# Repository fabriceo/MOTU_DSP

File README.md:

# MOTU_DSP
A DSP module compatible with MOTU 8A or MOTU 624

This repository contains Schematics, component placement for the MOTU_DSP board.
and additional documentation as PDF files.

this design is subject to Creative Commons Attribution Share-Alike 4.0 license

thread on diyaudio.com can be found here : https://www.diyaudio.com/forums/digital-line-level/333855-dsp-module-compatible-motu-8a-624-a.html

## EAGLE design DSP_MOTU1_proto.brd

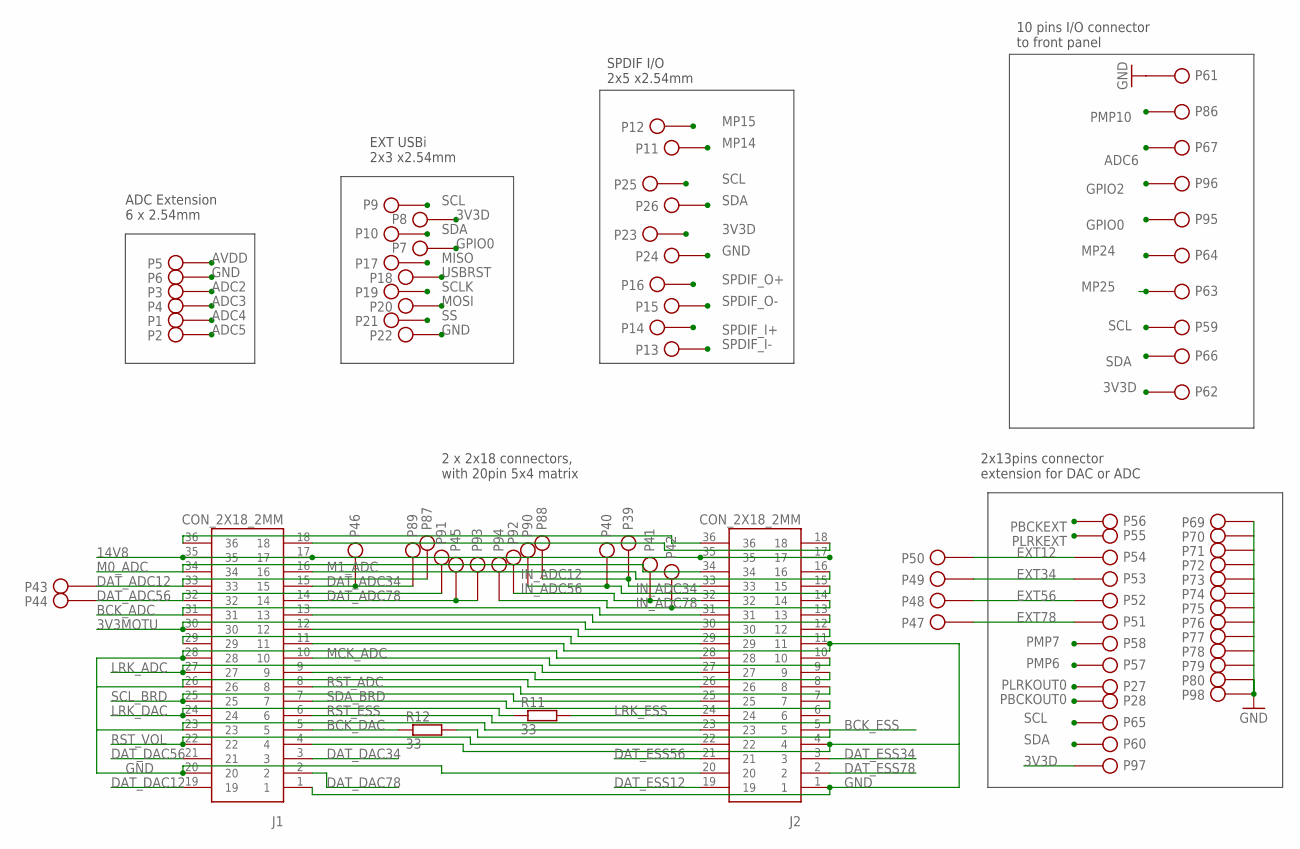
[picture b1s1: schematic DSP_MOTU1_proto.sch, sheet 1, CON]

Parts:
J1, J2: CON_2X18_2MM
P1, P2, P3, P4, P5, P6, P7, P8, P9, P10, P11, P12, P13, P14, P15, P16, P17, P18, P19, P20, P21, P22, P23, P24, P25, P26, P27, P28, P39, P40, P41, P42, P43, P44, P45, P46, P47, P48, P49, P50, P51, P52, P53, P54, P55, P56, P57, P58, P59, P60, P61, P62, P63, P64, P65, P66, P67, P69, P70, P71, P72, P73, P74, P75, P76, P77, P78, P79, P80, P86, P87, P88, P89, P90, P91, P92, P93, P94, P95, P96, P97, P98: PIN_254
R11, R12: 33; R0805

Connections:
3V3D: P8.1, P23.1, P62.1, P97.1; also elsewhere on the board
3V3MOTU: J1.30, J2.30
14V8: J1.17, J1.35, J2.17, J2.35; also elsewhere on the board
ADC2: P3.1; also elsewhere on the board
ADC3: P4.1; also elsewhere on the board
ADC4: P1.1; also elsewhere on the board
ADC5: P2.1; also elsewhere on the board
ADC6: P67.1; also elsewhere on the board
AVDD: P5.1; also elsewhere on the board
BCK_ADC: J1.31, J2.31; also elsewhere on the board
BCK_DAC: J1.5, R12.1; also elsewhere on the board
BCK_ESS: J2.5, R12.2; also elsewhere on the board
DAT_ADC12: J1.33, P43.1, P87.1
DAT_ADC34: J1.15, P46.1, P89.1
DAT_ADC56: J1.32, P44.1, P91.1
DAT_ADC78: J1.14, P45.1, P93.1
DAT_DAC12: J1.19; also elsewhere on the board
DAT_DAC34: J1.3; also elsewhere on the board
DAT_DAC56: J1.21; also elsewhere on the board
DAT_DAC78: J1.2; also elsewhere on the board
DAT_ESS12: J2.19; also elsewhere on the board
DAT_ESS34: J2.3; also elsewhere on the board
DAT_ESS56: J2.21; also elsewhere on the board
DAT_ESS78: J2.2; also elsewhere on the board
EXT12: P50.1, P54.1
EXT34: P49.1, P53.1
EXT56: P48.1, P52.1
EXT78: P47.1, P51.1
GND: J1.1, J1.4, J1.11, J1.20, J1.23, J1.26, J1.28, J2.1, J2.4, J2.11, J2.20, J2.23, J2.26, J2.28, P6.1, P22.1, P24.1, P61.1, P69.1, P70.1, P71.1, P72.1, P73.1, P74.1, P75.1, P76.1, P77.1, P78.1, P79.1, P80.1, P98.1; also elsewhere on the board
GPIO0: P7.1, P95.1; also elsewhere on the board
GPIO2: P96.1; also elsewhere on the board
IN_ADC12: J2.33, P39.1, P88.1
IN_ADC34: J2.15, P40.1, P90.1
IN_ADC56: J2.32, P41.1, P92.1
IN_ADC78: J2.14, P42.1, P94.1
LRK_ADC: J1.27, J2.27; also elsewhere on the board
LRK_DAC: J1.24, R11.1; also elsewhere on the board
LRK_ESS: J2.24, R11.2; also elsewhere on the board
M0_ADC: J1.34, J2.34
M1_ADC: J1.16, J2.16
MCK_ADC: J1.10, J2.10
MISO: P17.1; also elsewhere on the board
MOSI: P20.1; also elsewhere on the board
MP14: P11.1; also elsewhere on the board
MP15: P12.1; also elsewhere on the board
MP24: P64.1; also elsewhere on the board
MP25: P63.1; also elsewhere on the board
unnamed: J1.9, J2.9
unnamed: J1.29, J2.29
unnamed: J1.12, J2.12
unnamed: J1.13, J2.13
unnamed: J1.18, J2.18
unnamed: J1.36, J2.36
PBCKEXT: P56.1; also elsewhere on the board
PBCKOUT0: P28.1; also elsewhere on the board
PLRKEXT: P55.1; also elsewhere on the board
PLRKOUT0: P27.1; also elsewhere on the board
PMP6: P57.1; also elsewhere on the board
PMP7: P58.1; also elsewhere on the board
PMP10: P86.1; also elsewhere on the board
RST_ADC: J1.8, J2.8
RST_ESS: J1.6, J2.6
RST_VOL: J1.22, J2.22; also elsewhere on the board
SCL: P9.1, P25.1, P59.1, P65.1; also elsewhere on the board
SCLK: P19.1; also elsewhere on the board
SCL_BRD: J1.25, J2.25
SDA: P10.1, P26.1, P60.1, P66.1; also elsewhere on the board
SDA_BRD: J1.7, J2.7
SPDIF_I+: P14.1; also elsewhere on the board
SPDIF_I-: P13.1; also elsewhere on the board
SPDIF_O+: P16.1; also elsewhere on the board
SPDIF_O-: P15.1; also elsewhere on the board
SS: P21.1; also elsewhere on the board
USBRST: P18.1; also elsewhere on the board

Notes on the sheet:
ADC Extension 6 x 2.54mm
EXT USBi 2x3 x2.54mm
SPDIF I/O 2x5 x2.54mm
2x13pins connector extension for DAC or ADC
10 pins I/O connector to front panel
2 x 2x18 connectors, with 20pin 5x4 matrix

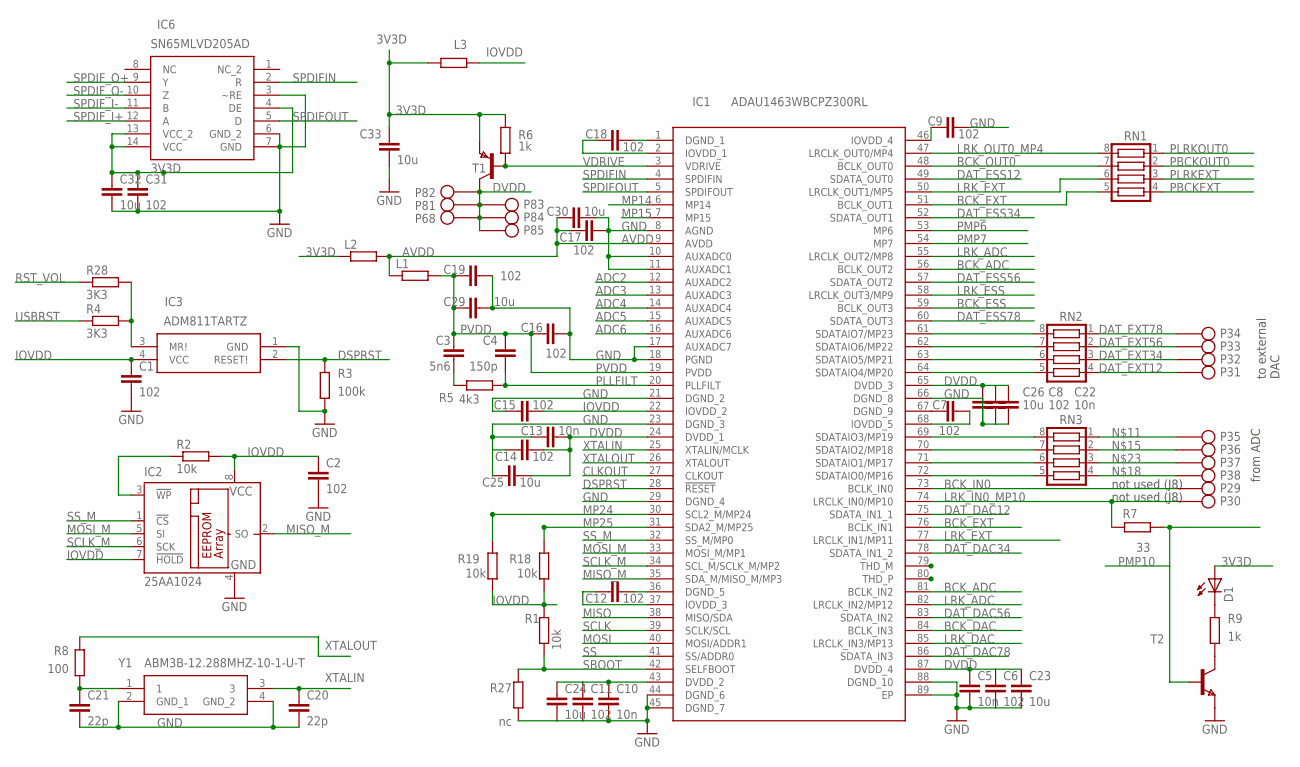
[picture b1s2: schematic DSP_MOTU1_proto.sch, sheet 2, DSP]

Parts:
C1, C2, C19, C31: 102; C0603
C3: 5n6; C0402
C4: 150p; C0402
C5, C10, C13, C22: 10n; C0402
C6, C7, C8, C9, C11, C12, C14, C15, C16, C17, C18: 102; C0402
C20, C21: 22p; C0402
C23, C24, C25, C26, C29, C30, C32, C33: 10u; C0805
D1: LEDCHIPLED_0805; CHIPLED_0805
IC1: ADAU1463WBCPZ300RL
IC2: 25AA1024; SO-08
IC3: ADM811TARTZ; SOT192P237X117-4N
IC6: SN65MLVD205AD; SOIC127P600X175-14N
L1, L2: R-EU_R0603; R0603
L3: R-EU_R0805; R0805
P29, P30, P31, P32, P33, P34, P35, P36, P37, P38, P68, P81, P82, P83, P84, P85: PIN_254
R1, R2, R18, R19: 10k; R0603
R3: 100k; R0603
R4, R28: 3K3; R0603
R5: 4k3; R0402
R6, R9: 1k; R0603
R7: 33; R0805
R8: 100; R0402
R27: nc; R0603
RN1, RN2, RN3: CTS742C083
T1: PNPSOT89; SOT89
T2: NPNSOT23; SOT-23
Y1: ABM3B-12.288MHZ-10-1-U-T; ABM3B

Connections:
3V3D: C31.1, C32.1, C33.1, D1.A, IC6.4 (DE), IC6.13 (VCC_2), IC6.14 (VCC), L2.1, L3.2, R6.1, T1.3 (E); also elsewhere on the board
ADC2: IC1.12 (AUXADC2); also elsewhere on the board
ADC3: IC1.13 (AUXADC3); also elsewhere on the board
ADC4: IC1.14 (AUXADC4); also elsewhere on the board
ADC5: IC1.15 (AUXADC5); also elsewhere on the board
ADC6: IC1.16 (AUXADC6); also elsewhere on the board
AVDD: C17.1, C30.1, IC1.9 (AVDD), L1.1, L2.2; also elsewhere on the board
BCK_ADC: IC1.56 (BCLK_OUT2), IC1.81 (BCLK_IN2); also elsewhere on the board
BCK_DAC: IC1.84 (BCLK_IN3); also elsewhere on the board
BCK_ESS: IC1.59 (BCLK_OUT3); also elsewhere on the board
BCK_EXT: IC1.51 (BCLK_OUT1), IC1.76 (BCLK_IN1), RN1.5
BCK_IN0: IC1.73 (BCLK_IN0), P29.1
BCK_OUT0: IC1.48 (BCLK_OUT0), RN1.7
CLKOUT: IC1.27 (CLKOUT)
DAT_DAC12: IC1.75 (SDATA_IN1_1); also elsewhere on the board
DAT_DAC34: IC1.78 (SDATA_IN1_2); also elsewhere on the board
DAT_DAC56: IC1.83 (SDATA_IN2); also elsewhere on the board
DAT_DAC78: IC1.86 (SDATA_IN3); also elsewhere on the board
DAT_ESS12: IC1.49 (SDATA_OUT0); also elsewhere on the board
DAT_ESS34: IC1.52 (SDATA_OUT1); also elsewhere on the board
DAT_ESS56: IC1.57 (SDATA_OUT2); also elsewhere on the board
DAT_ESS78: IC1.60 (SDATA_OUT3); also elsewhere on the board
DAT_EXT12: P31.1, RN2.4
DAT_EXT34: P32.1, RN2.3
DAT_EXT56: P33.1, RN2.2
DAT_EXT78: P34.1, RN2.1
DAT_IO12: IC1.72 (SDATAIO0/MP16), RN3.5
DSPRST: IC1.28 (!RESET), IC3.2 (RESET!), R3.1; also elsewhere on the board
DVDD: C5.1, C6.1, C8.1, C10.1, C11.1, C13.1, C14.1, C22.1, C23.1, C24.1, C25.1, C26.2, IC1.24 (DVDD_1), IC1.43 (DVDD_2), IC1.65 (DVDD_3), IC1.87 (DVDD_4), P68.1, P81.1, P82.1, P83.1, P84.1, P85.1, T1.2 (C), T1.2@1 (C)
GND: C1.2, C2.2, C5.2, C6.2, C7.2, C8.2, C9.2, C10.2, C11.2, C12.2, C13.2, C14.2, C15.2, C16.2, C17.2, C18.2, C19.2, C20.2, C21.2, C22.2, C23.2, C24.2, C25.2, C26.1, C29.2, C30.2, C31.2, C32.2, C33.2, IC1.1 (DGND_1), IC1.8 (AGND), IC1.10 (AUXADC0), IC1.11 (AUXADC1), IC1.17 (AUXADC7), IC1.18 (PGND), IC1.21 (DGND_2), IC1.23 (DGND_3), IC1.29 (DGND_4), IC1.36 (DGND_5), IC1.44 (DGND_6), IC1.45 (DGND_7), IC1.66 (DGND_8), IC1.67 (DGND_9), IC1.88 (DGND_10), IC1.89 (EP), IC2.4 (GND), IC3.1 (GND), IC6.3 (~RE), IC6.6 (GND_2), IC6.7 (GND), R3.2, R27.1, T2.2 (E), Y1.2 (GND_1), Y1.4 (GND_2); also elsewhere on the board
IOVDD: C1.1, C2.1, C7.1, C9.1, C12.1, C15.1, C18.1, IC1.2 (IOVDD_1), IC1.22 (IOVDD_2), IC1.37 (IOVDD_3), IC1.46 (IOVDD_4), IC1.68 (IOVDD_5), IC2.7 (!HOLD), IC2.8 (VCC), IC3.4 (VCC), L3.1, R1.2, R2.2, R18.1, R19.1
LRK_ADC: IC1.55 (LRCLK_OUT2/MP8), IC1.82 (LRCLK_IN2/MP12); also elsewhere on the board
LRK_DAC: IC1.85 (LRCLK_IN3/MP13); also elsewhere on the board
LRK_ESS: IC1.58 (LRCLK_OUT3/MP9); also elsewhere on the board
LRK_EXT: IC1.50 (LRCLK_OUT1/MP5), IC1.77 (LRCLK_IN1/MP11), RN1.6
LRK_IN0_MP10: IC1.74 (LRCLK_IN0/MP10), P30.1, R7.1
LRK_OUT0_MP4: IC1.47 (LRCLK_OUT0/MP4), RN1.8
MISO: IC1.38 (MISO/SDA); also elsewhere on the board
MISO_M: IC1.35 (SDA_M/MISO_M/MP3), IC2.2 (SO)
MOSI: IC1.40 (MOSI/ADDR1); also elsewhere on the board
MOSI_M: IC1.33 (MOSI_M/MP1), IC2.5 (SI)
MP14: IC1.6 (MP14); also elsewhere on the board
MP15: IC1.7 (MP15); also elsewhere on the board
MP24: IC1.30 (SCL2_M/MP24), R19.2; also elsewhere on the board
MP25: IC1.31 (SDA2_M/MP25), R18.2; also elsewhere on the board
unnamed: R9.2, T2.1 (C)
unnamed: IC1.64 (SDATAIO4/MP20), RN2.5
unnamed: IC1.63 (SDATAIO5/MP21), RN2.6
unnamed: IC2.3 (!WP), R2.1
unnamed: IC1.62 (SDATAIO6/MP22), RN2.7
unnamed: IC1.61 (SDATAIO7/MP23), RN2.8
unnamed: IC1.70 (SDATAIO2/MP18), RN3.7
unnamed: IC1.71 (SDATAIO1/MP17), RN3.6
unnamed: C21.1, R8.1, Y1.1
unnamed: P35.1, RN3.1
unnamed: C3.2, R5.2
unnamed: IC1.69 (SDATAIO3/MP19), RN3.8
unnamed: D1.C, R9.1
unnamed: P36.1, RN3.2
unnamed: P38.1, RN3.4
unnamed: P37.1, RN3.3
PBCKEXT: RN1.4; also elsewhere on the board
PBCKOUT0: RN1.2; also elsewhere on the board
PLLFILT: C4.2, IC1.20 (PLLFILT), R5.1
PLRKEXT: RN1.3; also elsewhere on the board
PLRKOUT0: RN1.1; also elsewhere on the board
PMP6: IC1.53 (MP6); also elsewhere on the board
PMP7: IC1.54 (MP7); also elsewhere on the board
PMP10: R7.2, T2.3 (B); also elsewhere on the board
PVDD: C3.1, C4.1, C16.1, C19.1, C29.1, IC1.19 (PVDD), L1.2
RST_VOL: R28.1; also elsewhere on the board
SBOOT: IC1.42 (SELFBOOT), R1.1, R27.2
SCLK: IC1.39 (SCLK/SCL); also elsewhere on the board
SCLK_M: IC1.34 (SCL_M/SCLK_M/MP2), IC2.6 (SCK)
SPDIFIN: IC1.4 (SPDIFIN), IC6.2 (R)
SPDIFOUT: IC1.5 (SPDIFOUT), IC6.5 (D)
SPDIF_I+: IC6.12 (A); also elsewhere on the board
SPDIF_I-: IC6.11 (B); also elsewhere on the board
SPDIF_O+: IC6.9 (Y); also elsewhere on the board
SPDIF_O-: IC6.10 (Z); also elsewhere on the board
SS: IC1.41 (SS/ADDR0); also elsewhere on the board
SS_M: IC1.32 (SS_M/MP0), IC2.1 (!CS)
USBRST: R4.1; also elsewhere on the board
USBRST_: IC3.3 (MR!), R4.2, R28.2
VDRIVE: IC1.3 (VDRIVE), R6.2, T1.1 (B)
XTALIN: C20.1, IC1.25 (XTALIN/MCLK), Y1.3
XTALOUT: IC1.26 (XTALOUT), R8.2

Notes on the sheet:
from ADC
to external DAC
not used (J8)

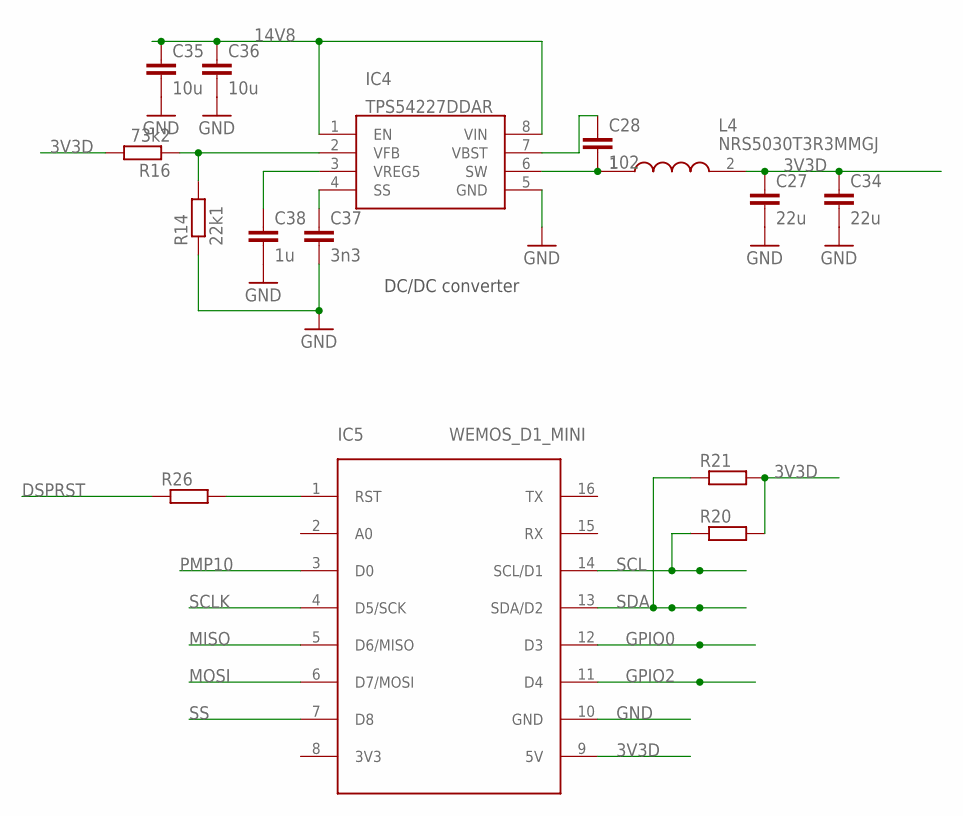
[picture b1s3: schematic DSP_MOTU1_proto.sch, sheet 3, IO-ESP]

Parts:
C27, C34: 22u; C1206
C28: 102; C0603
C35, C36: 10u; C1210
C37: 3n3; C0603
C38: 1u; C0603K
IC4: TPS54227DDAR; SOIC127P600X170-8N
IC5: WEMOS_D1_MINI
L4: NRS5030T3R3MMGJ; INDC4949X330N
R14: 22k1; R0603
R16: 73k2; R0603
R20, R21, R26: R-EU_R0603; R0603

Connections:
3V3D: C27.1, C34.1, IC5.9 (5V), L4.2, R16.2, R20.2, R21.2; also elsewhere on the board
14V8: C35.1, C36.1, IC4.1 (EN), IC4.8 (VIN); also elsewhere on the board
D1_RST: IC5.1 (RST), R26.2
DSPRST: R26.1; also elsewhere on the board
GND: C27.2, C34.2, C35.2, C36.2, C37.2, C38.2, IC4.5 (GND), IC5.10 (GND), R14.1; also elsewhere on the board
GPIO0: IC5.12 (D3); also elsewhere on the board
GPIO2: IC5.11 (D4); also elsewhere on the board
MISO: IC5.5 (D6/MISO); also elsewhere on the board
MOSI: IC5.6 (D7/MOSI); also elsewhere on the board
unnamed: C28.2, IC4.6 (SW), L4.1
unnamed: C28.1, IC4.7 (VBST)
unnamed: C37.1, IC4.4 (SS)
unnamed: C38.1, IC4.3 (VREG5)
unnamed: IC4.2 (VFB), R14.2, R16.1
PMP10: IC5.3 (D0); also elsewhere on the board
SCL: IC5.14 (SCL/D1), R20.1; also elsewhere on the board
SCLK: IC5.4 (D5/SCK); also elsewhere on the board
SDA: IC5.13 (SDA/D2), R21.1; also elsewhere on the board
SS: IC5.7 (D8); also elsewhere on the board

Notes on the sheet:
DC/DC converter

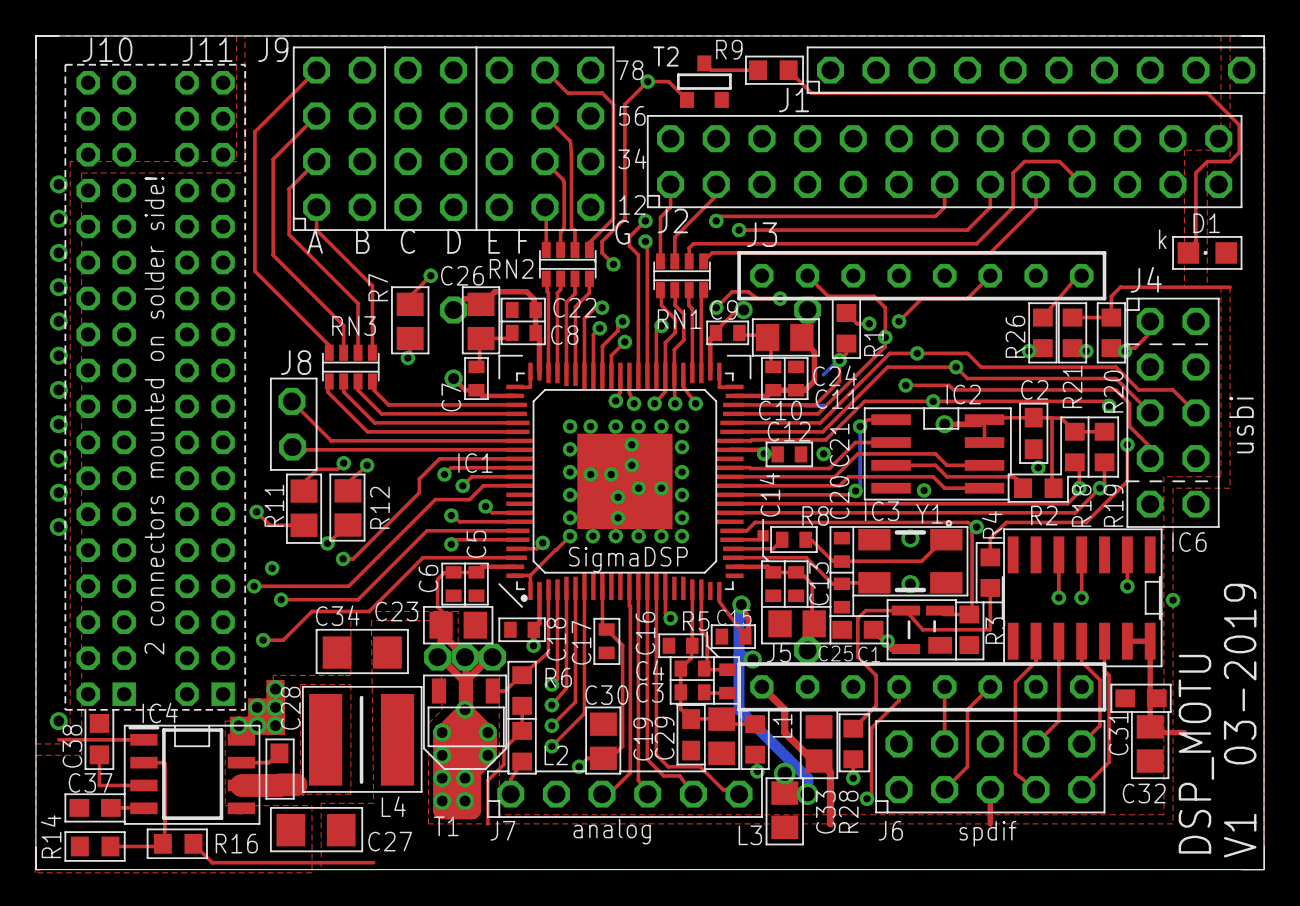
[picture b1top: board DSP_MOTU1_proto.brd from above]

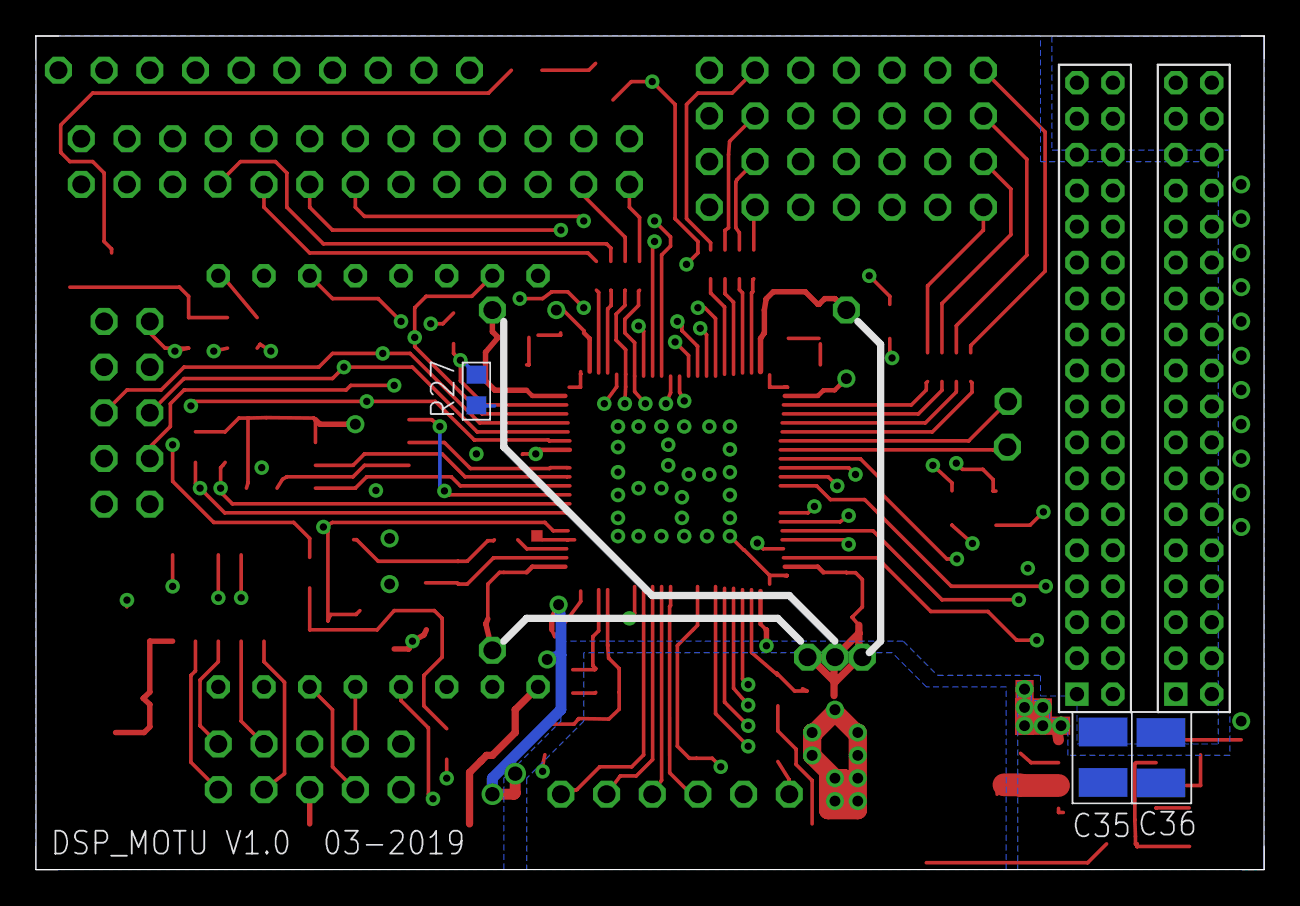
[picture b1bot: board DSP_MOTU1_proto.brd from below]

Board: 4 copper layers, 68.3 x 46.4 mm, 175 parts (3 on the bottom side), 123 nets.
